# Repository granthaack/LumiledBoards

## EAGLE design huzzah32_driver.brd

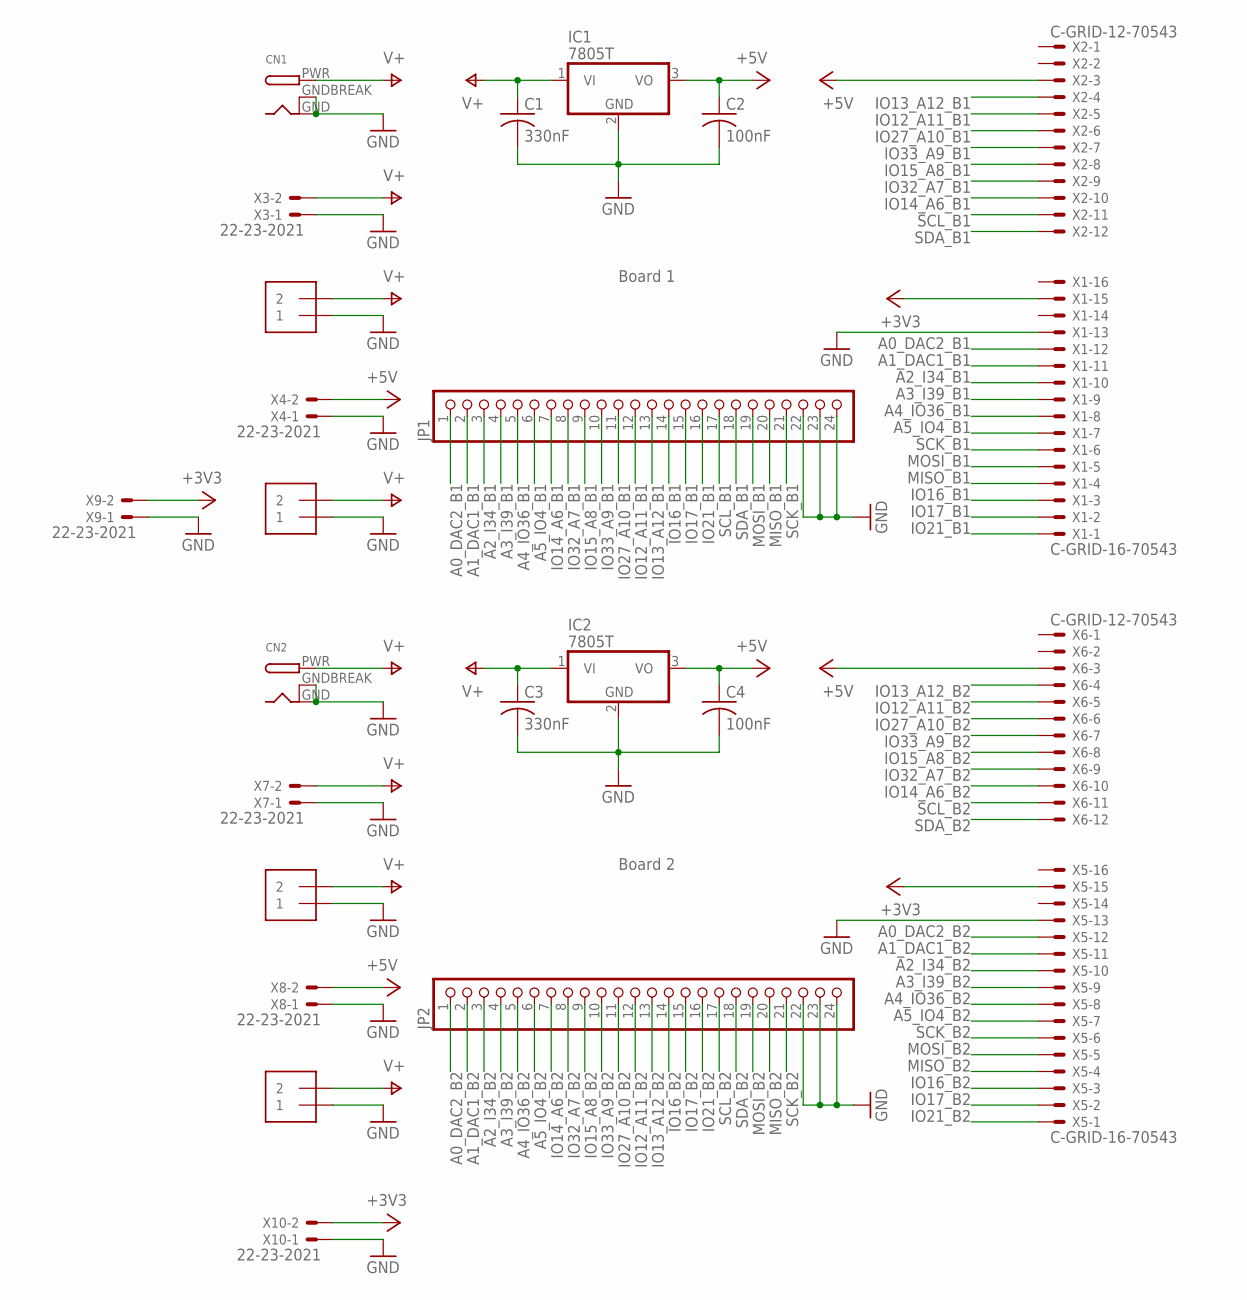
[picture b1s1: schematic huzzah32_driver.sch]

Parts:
C1, C3: 330nF; C050-035X075
C2, C4: 100nF; C050-035X075
CN1, CN2: DCBARRELPTH; DCJACK_2MM_PTH
IC1, IC2: 7805T; TO220H
J1, J2, J3, J4: 1X2-3.5MM
JP1, JP2: PINHD-1X24; 1X24
X1, X5: C-GRID-16-70543; 70543-16
X2, X6: C-GRID-12-70543; 70543-12
X3, X4, X7, X8, X9, X10: 22-23-2021

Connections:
+3V3: X1.15, X5.15, X9.2, X10.2
+5V: C2.1, C4.1, IC1.3 (VO), IC2.3 (VO), X2.3, X4.2, X6.3, X8.2
A0_DAC2_B1: JP1.1, X1.12
A0_DAC2_B2: JP2.1, X5.12
A1_DAC1_B1: JP1.2, X1.11
A1_DAC1_B2: JP2.2, X5.11
A2_I34_B1: JP1.3, X1.10
A2_I34_B2: JP2.3, X5.10
A3_I39_B1: JP1.4, X1.9
A3_I39_B2: JP2.4, X5.9
A4_IO36_B1: JP1.5, X1.8
A4_IO36_B2: JP2.5, X5.8
A5_IO4_B1: JP1.6, X1.7
A5_IO4_B2: JP2.6, X5.7
GND: C1.2, C2.2, C3.2, C4.2, CN1.GND, CN1.GNDBREAK, CN2.GND, CN2.GNDBREAK, IC1.2 (GND), IC2.2 (GND), J1.1, J2.1, J3.1, J4.1, JP1.22, JP1.23, JP1.24, JP2.22, JP2.23, JP2.24, X1.13, X3.1, X4.1, X5.13, X7.1, X8.1, X9.1, X10.1
IO12_A11_B1: JP1.12, X2.5
IO12_A11_B2: JP2.12, X6.5
IO13_A12_B1: JP1.13, X2.4
IO13_A12_B2: JP2.13, X6.4
IO14_A6_B1: JP1.7, X2.10
IO14_A6_B2: JP2.7, X6.10
IO15_A8_B1: JP1.9, X2.8
IO15_A8_B2: JP2.9, X6.8
IO16_B1: JP1.14, X1.3
IO16_B2: JP2.14, X5.3
IO17_B1: JP1.15, X1.2
IO17_B2: JP2.15, X5.2
IO21_B1: JP1.16, X1.1
IO21_B2: JP2.16, X5.1
IO27_A10_B1: JP1.11, X2.6
IO27_A10_B2: JP2.11, X6.6
IO32_A7_B1: JP1.8, X2.9
IO32_A7_B2: JP2.8, X6.9
IO33_A9_B1: JP1.10, X2.7
IO33_A9_B2: JP2.10, X6.7
MISO_B1: JP1.20, X1.4
MISO_B2: JP2.20, X5.4
MOSI_B1: JP1.19, X1.5
MOSI_B2: JP2.19, X5.5
SCK_B1: JP1.21, X1.6
SCK_B2: JP2.21, X5.6
SCL_B1: JP1.17, X2.11
SCL_B2: JP2.17, X6.11
SDA_B1: JP1.18, X2.12
SDA_B2: JP2.18, X6.12
V+: C1.1, C3.1, CN1.PWR, CN2.PWR, IC1.1 (VI), IC2.1 (VI), J1.2, J2.2, J3.2, J4.2, X3.2, X7.2

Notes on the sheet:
Board 1
Board 2

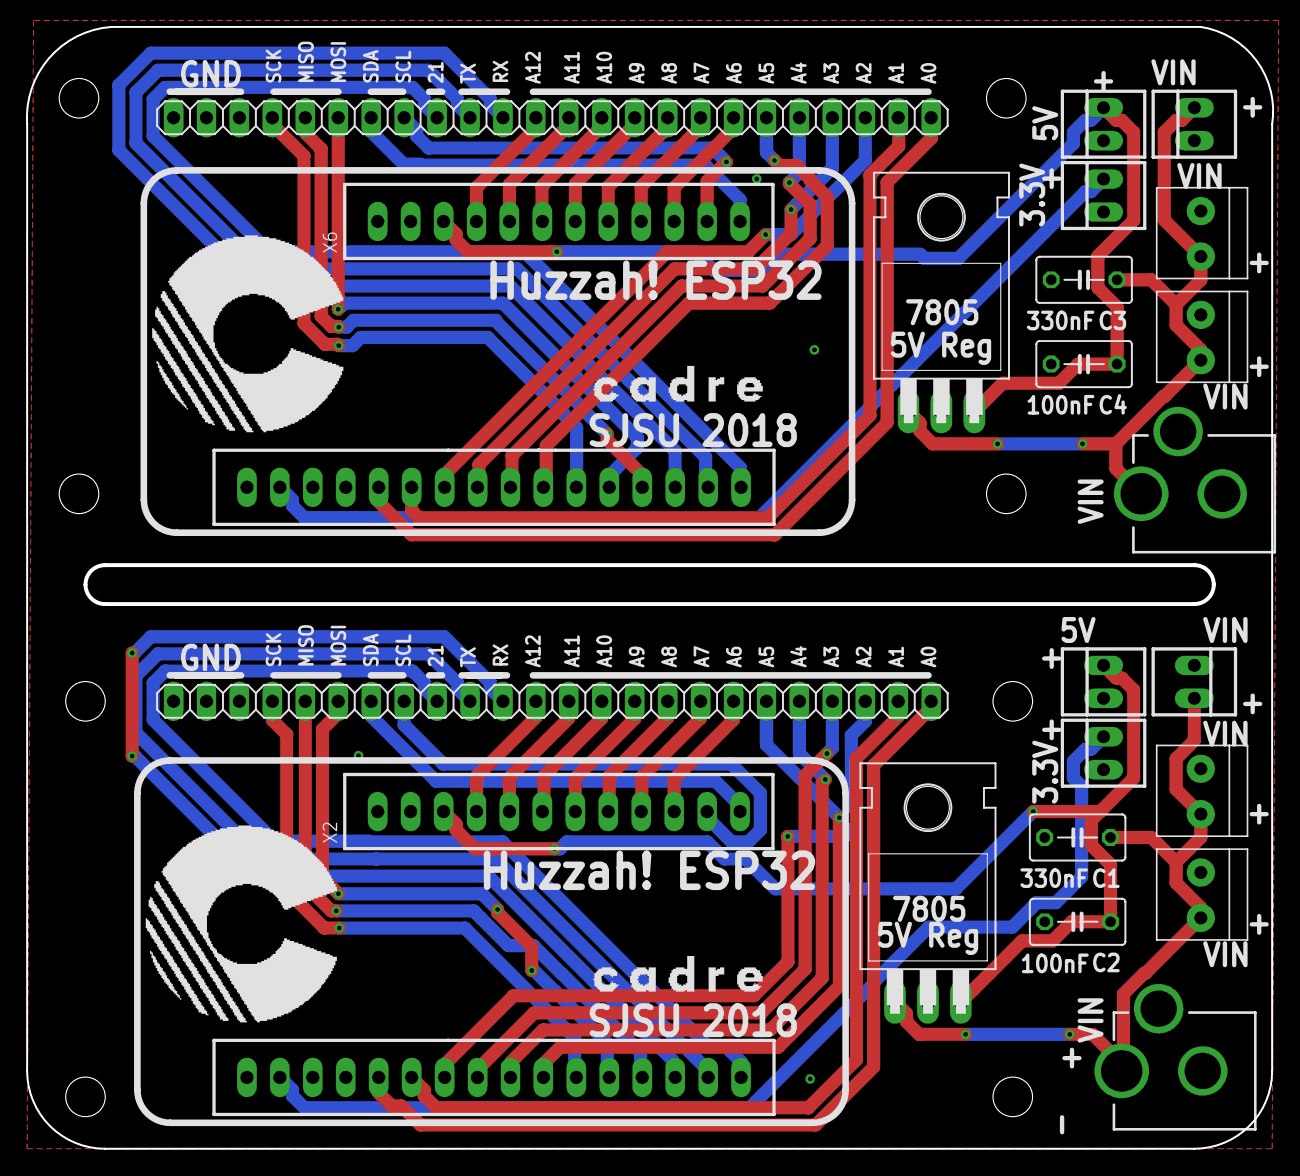
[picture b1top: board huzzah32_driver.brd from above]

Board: 2 copper layers, 96.1 x 86.5 mm, 24 parts (0 on the bottom side), 46 nets.

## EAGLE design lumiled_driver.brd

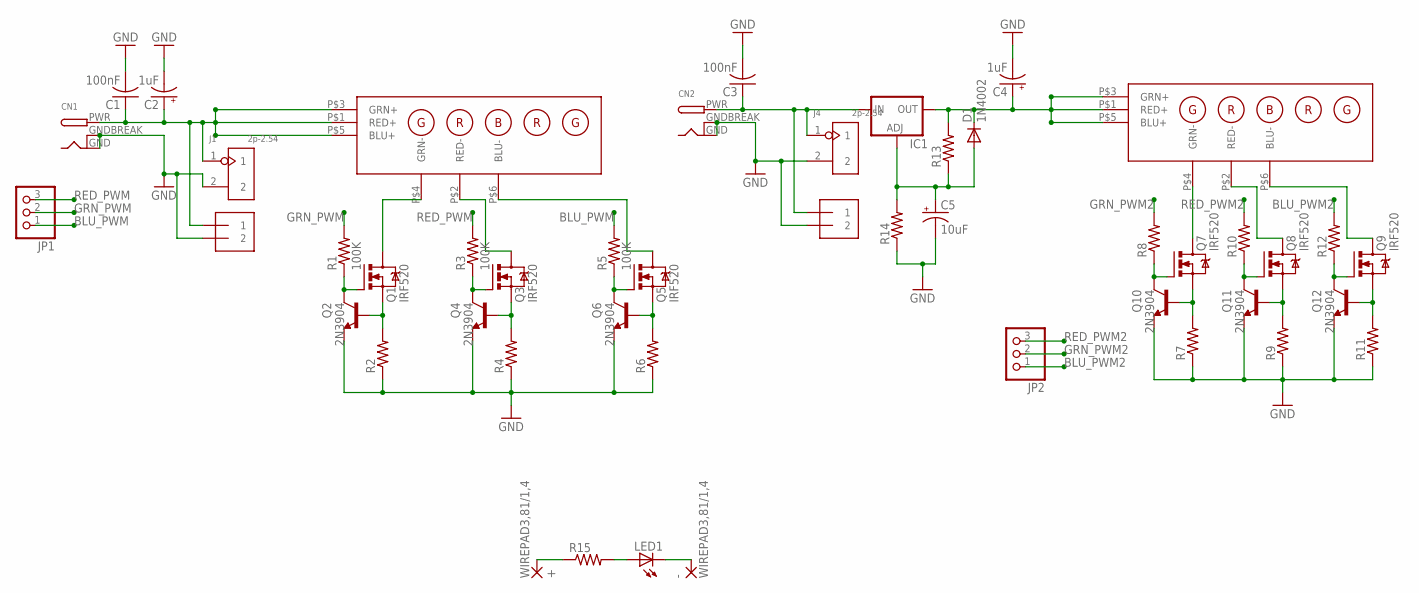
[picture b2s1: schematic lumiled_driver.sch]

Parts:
+: WIREPAD3,81/1,4; 3,81/1,4
-: WIREPAD3,81/1,4; 3,81/1,4
C1, C3: 100nF; C025-024X044
C2, C4: 1uF; TT2D5
C5: 10uF; TT2D5
CN1, CN2: DCBARRELPTH; DCJACK_2MM_PTH
D1: 1N4002; DO41-10
IC1: LM317TL; 317TL
J1, J4: 2p-2.54; H2-2.54
J2, J3: 1X2-3.5MM
JP1, JP2: PINHD-1X3; 1X03
LED1: LED3MM
Q1, Q3, Q5, Q7, Q8, Q9: IRF520; TO220BV
Q2, Q4, Q6, Q10, Q11, Q12: 2N3904; TO92
R1, R3, R5: 100K; 0411/12
R2, R4, R6, R7, R8, R9, R10, R11, R12, R13, R14: R-US_0411/12; 0411/12
R15: R-US_0207/12; 0207/12
U$1, U$2: LUMILED_PARALLEL; LED_PAR

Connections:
+VIN: C1.1, C2.+, CN1.PWR, J1.1, J2.1, U$1.P$1 (RED+), U$1.P$3 (GRN+), U$1.P$5 (BLU+)
+VIN1: C4.+, D1.C, IC1.2 (OUT), R13.2, U$2.P$1 (RED+), U$2.P$3 (GRN+), U$2.P$5 (BLU+)
BLU_PWM: JP1.1, R5.2
BLU_PWM2: JP2.1, R12.2
GND: C1.2, C2.-, C3.2, C4.-, C5.-, CN1.GND, CN1.GNDBREAK, CN2.GND, CN2.GNDBREAK, J1.2, J2.2, J3.2, J4.2, Q2.3 (E), Q4.3 (E), Q6.3 (E), Q10.3 (E), Q11.3 (E), Q12.3 (E), R2.1, R4.1, R6.1, R7.1, R9.1, R11.1, R14.1
GRN_PWM: JP1.2, R1.2
GRN_PWM2: JP2.2, R8.2
unnamed: Q7.D, U$2.P$4 (GRN-)
unnamed: Q7.G, Q10.1 (C), R8.1
unnamed: Q8.G, Q11.1 (C), R10.1
unnamed: Q9.G, Q12.1 (C), R12.1
unnamed: Q7.S, Q10.2 (B), R7.2
unnamed: Q8.S, Q11.2 (B), R9.2
unnamed: Q9.S, Q12.2 (B), R11.2
unnamed: Q8.D, U$2.P$2 (RED-)
unnamed: Q9.D, U$2.P$6 (BLU-)
unnamed: Q1.D, U$1.P$4 (GRN-)
unnamed: C3.1, CN2.PWR, IC1.3 (IN), J3.1, J4.1
unnamed: C5.+, D1.A, IC1.1 (ADJ), R13.1, R14.2
unnamed: Q1.G, Q2.1 (C), R1.1
unnamed: Q3.G, Q4.1 (C), R3.1
unnamed: Q5.G, Q6.1 (C), R5.1
unnamed: Q1.S, Q2.2 (B), R2.2
unnamed: Q3.S, Q4.2 (B), R4.2
unnamed: Q5.S, Q6.2 (B), R6.2
unnamed: Q3.D, U$1.P$2 (RED-)
unnamed: Q5.D, U$1.P$6 (BLU-)
unnamed: LED1.A, R15.2
unnamed: +.1, R15.1
unnamed: -.1, LED1.K (C)
RED_PWM: JP1.3, R3.2
RED_PWM2: JP2.3, R10.2

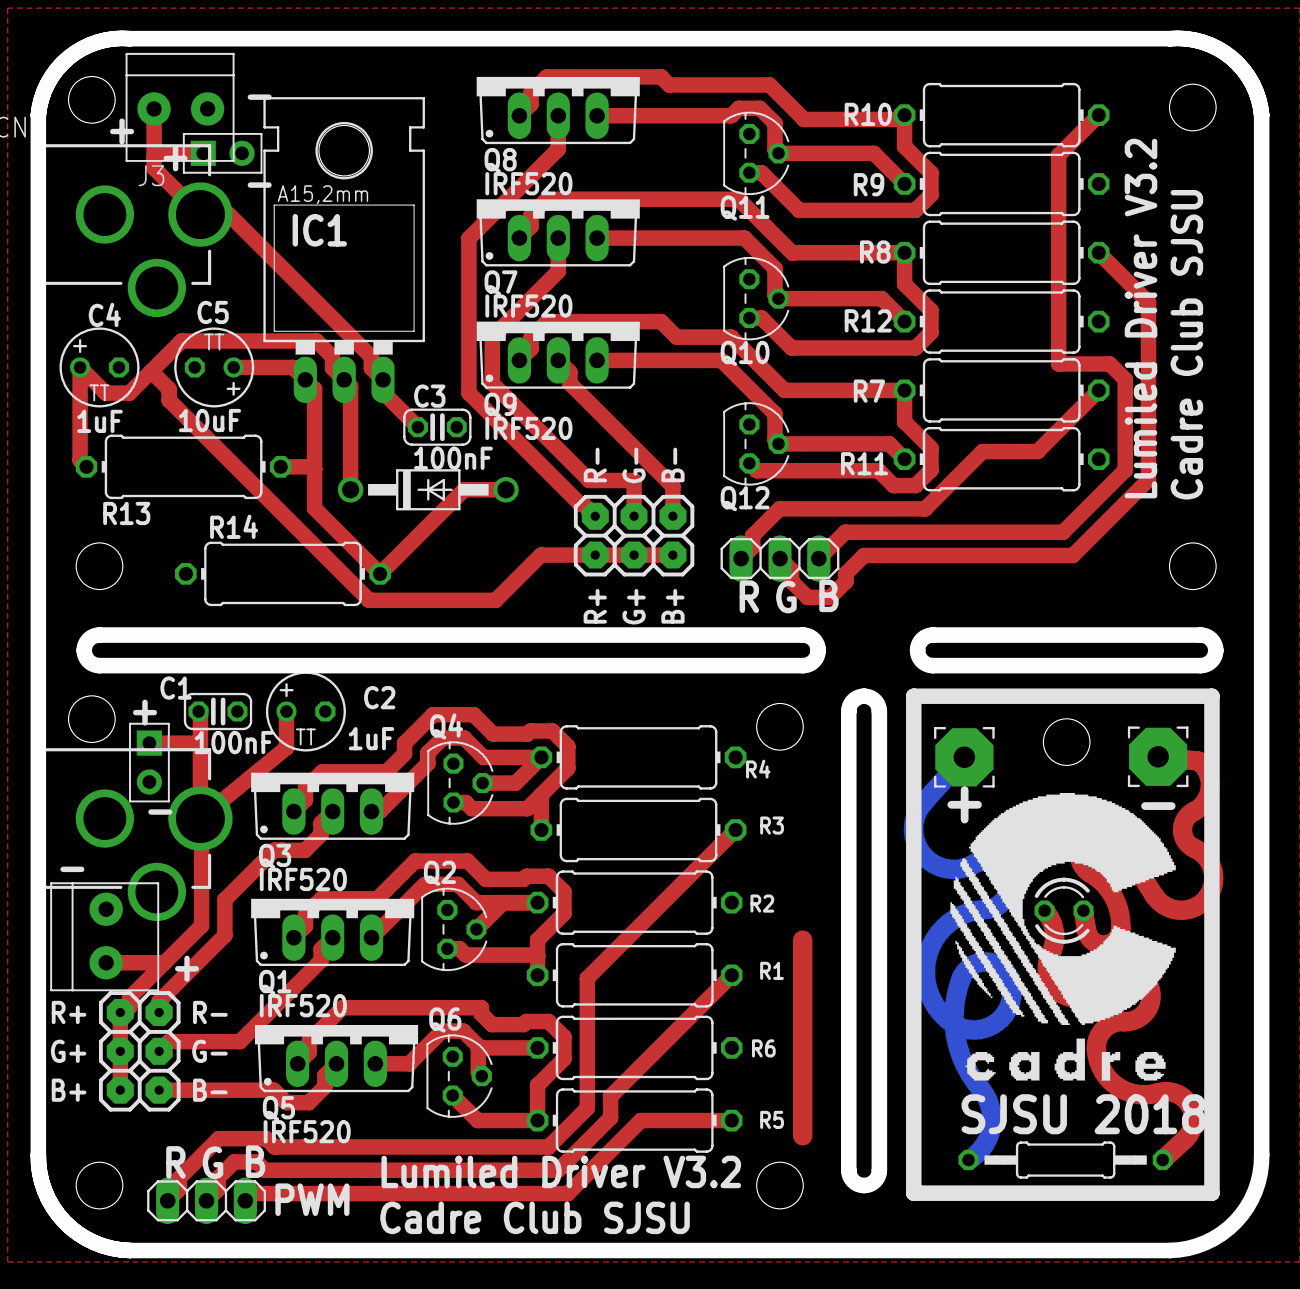
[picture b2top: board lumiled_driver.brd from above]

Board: 2 copper layers, 80.0 x 79.3 mm, 47 parts (0 on the bottom side), 32 nets.

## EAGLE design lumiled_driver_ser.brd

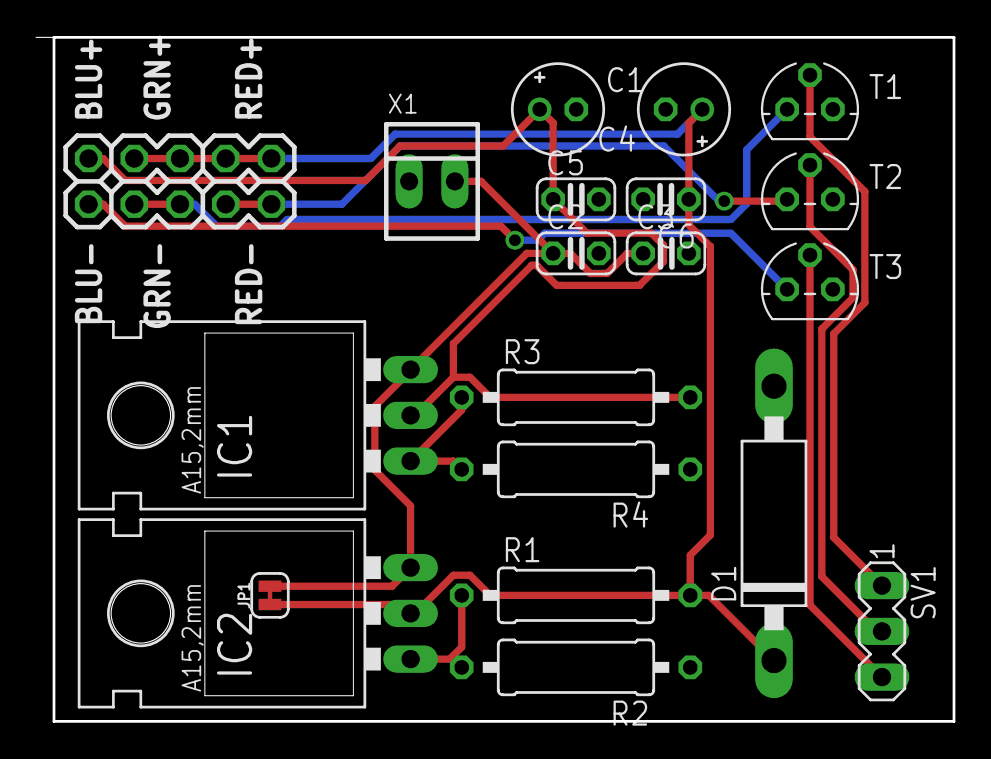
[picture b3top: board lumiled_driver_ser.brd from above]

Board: 2 copper layers, 51.0 x 38.0 mm, 20 parts (0 on the bottom side), 12 nets.

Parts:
C1, C4: 10uF; E2-5
C2: 1uF; C025-024X044
C3, C5, C6: 100nF; C025-024X044
D1: C1702-15
IC1, IC2: 317TL
JP1: 12V BYPASS; SMT-JUMPER_2_NC_TRACE_SILK
R1, R2, R3, R4: 0309/12
SV1: MA03-1
T1, T2, T3: TO92
U$1: LUMILED_5LED; MA05-2
X1: PWR; 22-23-2021

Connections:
+VIN: C2.1, C3.1, IC1.3, IC2.3, JP1.2, X1.2
BLU_PWM: SV1.3, T3.2
GND: C1.-, C2.2, C3.2, C4.-, C5.2, C6.2, D1.A, R2.1, R4.1, T1.1, T2.1, T3.1, X1.1
GRN_PWM: SV1.1, T1.2
unnamed: T1.3, U$1.6, U$1.8
unnamed: T2.3, U$1.2, U$1.4
unnamed: T3.3, U$1.10
unnamed: C1.+, C5.1, IC1.2, R3.2, U$1.9
unnamed: C4.+, C6.1, D1.C, IC2.2, JP1.1, R1.2, U$1.1, U$1.3, U$1.5, U$1.7
unnamed: IC2.1, R1.1, R2.2
unnamed: IC1.1, R3.1, R4.2
RED_PWM: SV1.2, T2.2

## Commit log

2017-12-24 -first commit
2017-12-24 -added schematic
2017-12-30 -fixed a capacitor value -added screenshots of the board headers for the LED boards
2017-12-31 -added a design that allows us to drive the LEDs in series
2017-12-31 -added pictures of the schematic
2018-01-13 -added zener to series board -started work on board layout
2018-01-14 -cleaned up board labels
2018-02-01 -changed design to use MOSFETs
2018-02-19 just a commit
2018-03-03 -wow it's been a while since the last commit
2018-03-03 -sent out to elecrow for fabrication
2018-04-26 frankly, I've forgotten all the changes I've made but it's a lot
2018-05-02 Started work on the Huzzah32 board
2018-05-04 I've been working on this for like 6 hours and now it's 4am you expect me to write a commit message? -finished the board
2018-05-05 -fixed the issue with the backwards pins

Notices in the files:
parts and their libraries:
SparkFun-Jumpers: Licensing: Creative Commons ShareAlike 4.0 International - https://creativecommons.org/licenses/by-sa/4.0
